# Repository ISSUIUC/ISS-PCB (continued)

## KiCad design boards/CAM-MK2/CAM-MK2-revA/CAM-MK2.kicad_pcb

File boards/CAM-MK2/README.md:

# CAM MK2

The CAM series of custom camera control boards is intended to power and command onboard RunCam FPV cameras for reliable recording of onboard rocket footage.

Bouncing back from the failure of CAM MK1, the team’s onboard video system saw a big leap forward with the success of CAM MK2. In addition to shrinking board size by 33%, MK2 features revamped power circuitry and additional camera control features, making it more flexible as it seeks to ensure proper operation of the vehicle’s cameras for the collection of visual data on in-flight events (and capturing some really cool views). Closely integrated with MIDAS through inter-board CAN and I2C interfaces, CAM is capable of receiving remote commands based on either the MIDAS FSM or telemetry communications from the ground station. As the first peripheral board designed to talk directly with MIDAS, CAM serves as a pioneer of connectivity in the MIDAS ecosystem and has flown successfully several times.

Read more about CAM, MIDAS and the surrounding avionics systems in the [MIDAS MK2 Report](https://uofi.box.com/s/k0ad6ryhxbzwpdwt33lxyxuxpivv3qhj).

# Schematics

Printable PDF schematics, diagrams, and layouts for CAM MK2.1 revA can be found in the PDFs and images folders.

# Graphics

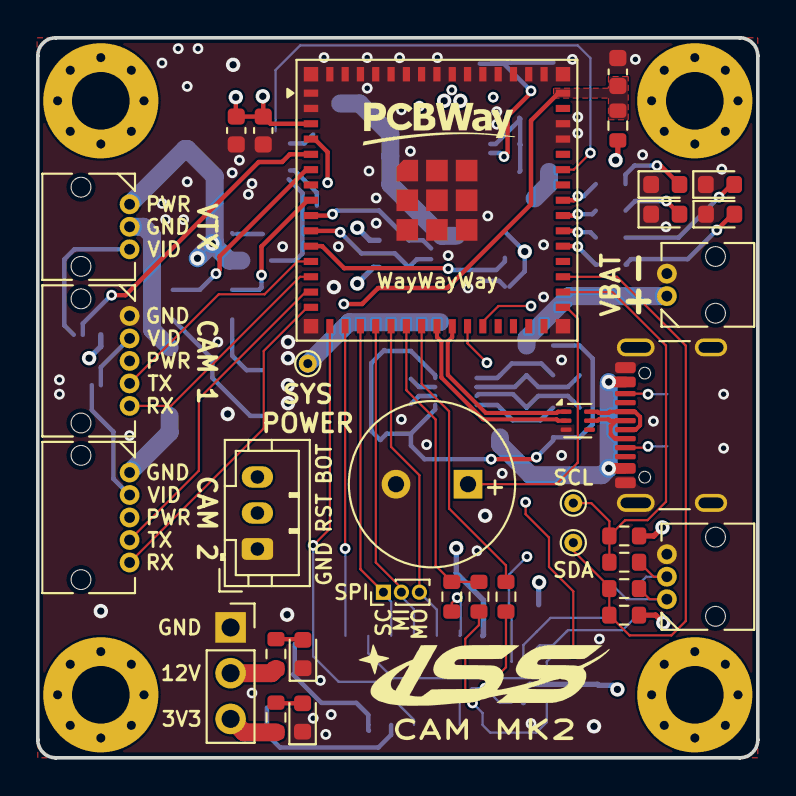
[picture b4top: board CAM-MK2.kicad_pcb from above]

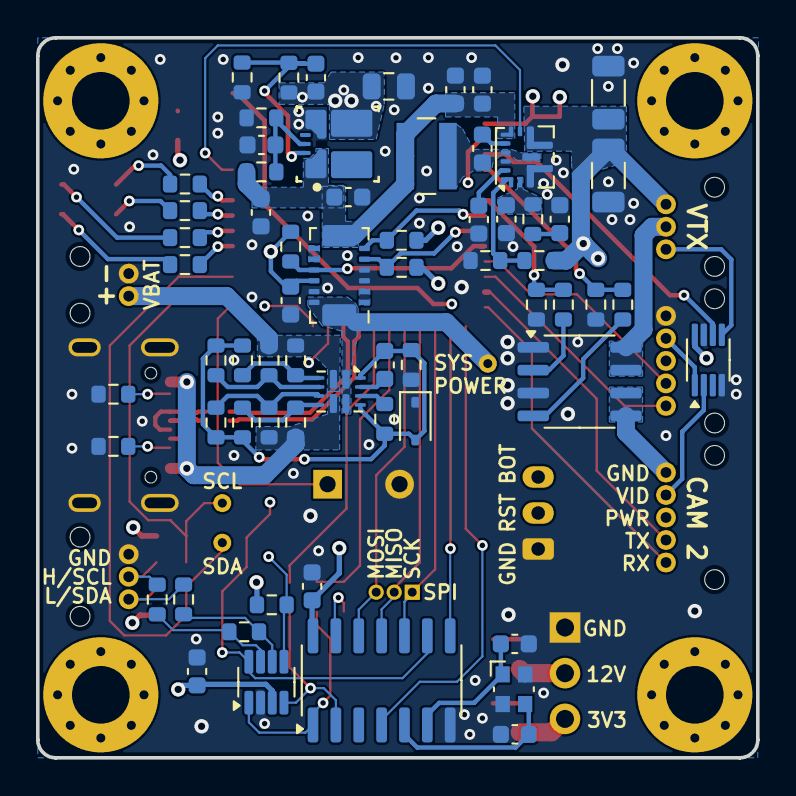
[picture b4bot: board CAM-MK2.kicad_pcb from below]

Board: 4 copper layers, 40.0 x 40.0 mm, 102 parts (64 on the bottom side), 81 nets.

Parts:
BZ101: Buzzer; MagneticBuzzer_PUI_AT-0927-TT-6-R
C101, C102, C111: 22pF; C_0603_1608Metric
C103, C104: 10uF; C_0603_1608Metric
C105, C106, C108, C110, C114, C116, C121: 0.1uF; C_0603_1608Metric
C107: 10nF; C_0603_1608Metric
C109: 2.2uF; C_0603_1608Metric
C112: 47nF; C_0603_1608Metric
C113: 27pF; C_0603_1608Metric
C115: 33uF; C_0805_2012Metric
C117, C118: 47uF; C_1206_3216Metric
C119, C120: 1uF; C_0603_1608Metric
C122: 22uF; C_0603_1608Metric
D101, D104: RED LED; LED_0603_1608Metric
D102, D105: ORANGE LED; LED_0603_1608Metric
D103: BAS416; D_SOD-323
D106: GREEN LED; LED_0603_1608Metric
D107: BLUE LED; LED_0603_1608Metric
H101, H102, H103, H104: MountingHole; MountingHole_3.2mm_M3_Pad_Via
J101: USB4105-GF-A; USB_C_Receptacle_GCT_USB4105-xx-A_16P_TopMnt_Horizontal
J102: 2157601002; Molex_Micro-Lock_2200980271_1x02_P1.25mm_Horizontal
J103, J105: Conn_01x03; Molex_Micro-Lock_2200980371_1x03_P1.25mm_Horizontal
J104, J106: Conn_01x05; Molex_Micro-Lock_2200980571_1x05_P1.25mm_Horizontal
J107: Conn_01x03; JST_PH_B3B-PH-K_1x03_P2.00mm_Vertical
J108: Conn_01x03; PinSocket_1x03_P2.54mm_Vertical
J109: Conn_01x03; PinHeader_1x03_P1.00mm_Vertical
L101: 4.7uH; L_Wuerth_MAPI-4030
Q101: DMNH6022SSDQ; SO-8_3.9x4.9mm_P1.27mm
R101: 22.1k; R_0603_1608Metric
R102, R108, R116, R123, R124, R126, R128, R130: 10k; R_0603_1608Metric
R105, R106: 5.1k; R_0603_1608Metric
R107: 14.3k; R_0603_1608Metric
R109: 135k; R_0603_1608Metric
R110: 30k; R_0603_1608Metric
R111: 931k; R_0603_1608Metric
R112: 48.7k; R_0603_1608Metric
R113, R115, R141, R142, R143, R144: 470; R_0603_1608Metric
R114: 120; R_0603_1608Metric
R117, R122: 4.7k; R_0603_1608Metric
R118, R119, R120, R121, R131, R137, R138, R139: 0; R_0603_1608Metric
R125, R136: 36k; R_0603_1608Metric
R127: 12k; R_0603_1608Metric
R129: 75k; R_0603_1608Metric
R132, R134: 1k; R_0603_1608Metric
R133, R135: 3.3k; R_0603_1608Metric
R140: 20k; R_0603_1608Metric
R145, R146: 2.2k; R_0603_1608Metric
TP101, TP102, TP103: TestPoint; TestPoint_THTPad_D1.0mm_Drill0.5mm
U101: ECMF02-2AMX6; ST_UQFN-6L_1.5x1.7mm_P0.5mm
U102: MCP2518FDT-xSL; SOIC-14_3.9x8.7mm_P1.27mm
U103: TPSM863252; QFN-FCMOD-RDX0007A
U104: TPS61288; Texas_VQFN-HR-20_3x2.5mm_P0.5mm_RQQ0011A
U105: TCAN337G; SOT-23-8
U106: INA745x; VQFN-REL0014B
U107: 74LVC2G157; VSSOP-8_2.3x2mm_P0.5mm
U108: TPS2121; Texas_VQFN-HR-12_2x2.5mm_P0.5mm
U109: ESP32-S3-MINI-1U; ESP32-S2-MINI-1U
Y101: 40MHz; Crystal_SMD_Abracon_ABM10-4Pin_2.5x2.0mm

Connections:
+3V3: C110.2, C111.1, C114.1, C115.1, C116.2, C121.1, C122.1, J108.3, R108.1, R109.1, R113.1, R116.1, R117.1, R122.1, R140.2, R145.2, R146.1, U102.14 (VDD), U103.3 (VOUT), U105.3 (VCC), U106.11 (VS), U107.8 (VCC), U109.3 (3V3)
+12V: C117.1, C118.1, J104.3, J105.1, J106.3, J108.2, R111.1, R115.1, U104.5 (VOUT)
/12V_EN: U104.6 (EN), U109.40 (RXD0)
/BOOT_SW: J107.3, U109.4 (IO0)
/BUZZER: BZ101.1 (-), U109.31 (IO35)
/CAM_2_POW: J106.1, Q101.5 (D2), Q101.6 (D2)
/CANH: R114.2, R120.1, U105.7 (CANH)
/CANL: R114.1, R118.1, U105.6 (CANL)
/CAN_1: R137.1, R138.1, U109.21 (IO17)
/CAN_2: R139.1, U109.22 (IO18)
/CAN_FAULT: R108.2, U105.5 (FAULT), U109.26 (IO26)
/CAN_NCS: R137.2, U102.13 (NCS)
/CAN_NINT: U102.4 (~INT), U109.16 (IO12)
/CAN_NINT1: U102.8 (~INT1/GPIO1), U109.17 (IO13)
/CAN_RXD: R139.2, U102.2 (RXCAN), U105.4 (RXD)
/CAN_SLNT: U102.9 (~INT0/GPIO0/XSTBY), U105.8 (S), U109.25 (IO21)
/CAN_TXD: R138.2, U102.1 (TXCAN), U105.1 (TXD)
/D+: J101.A6 (D+), J101.B6 (D+), U101.6 (D+_out)
/D-: J101.A7 (D-), J101.B7 (D-), U101.5 (D-_out)
/LED_BLUE: R144.1, U109.35 (IO39)
/LED_GREEN: R143.1, U109.36 (IO40)
/LED_ORANGE: R142.1, U109.37 (IO41)
/LED_RED: R141.1, U109.38 (IO42)
/ON_OFF_2: R134.2, R135.1, U109.6 (IO2)
/ON_OFF_VTX: R132.2, R133.1, U109.8 (IO4)
/RESET_SW: C120.1, J107.2, R140.1, U109.45 (EN)
/RX_1: J104.5, U109.13 (IO9)
/RX_2: J106.5, U109.15 (IO11)
/SCL: R121.1, R146.2, TP102.1, U109.32 (IO36)
/SDA: R119.1, R145.1, TP103.1, U109.33 (IO37)
/SENSE_ALERT: R116.2, U106.10 (ALERT), U109.11 (IO7)
/SENSE_SCL: R122.2, U106.6 (SCL), U109.9 (IO5)
/SENSE_SDA: R117.2, U106.5 (SDA), U109.10 (IO6)
/SPI_MISO: J109.2, U102.11 (SDI), U109.19 (IO15)
/SPI_MOSI: J109.3, U102.12 (SDO), U109.20 (IO16)
/SPI_SCK: J109.1, U102.10 (SCK), U109.18 (IO14)
/SYS_POWER: TP101.1, U106.13 (VBUS), U106.14 (IS+), U108.1 (OUT), U108.8 (OUT)
/TX_1: J104.4, U109.12 (IO8)
/TX_2: J106.4, U109.14 (IO10)
/USB_D+: U101.1 (D+_in), U109.24 (IO20)
/USB_D-: U101.2 (D-_in), U109.23 (IO19)
/USB_POWER: J101.A4 (VBUS), J101.A9 (VBUS), J101.B4 (VBUS), J101.B9 (VBUS), R123.1, R125.1, U108.7 (IN1)
/VBAT: J102.1, R127.1, R129.1, U108.2 (IN2)
/VIDEO_1: J104.2, U107.1 (A)
/VIDEO_2: J106.2, U107.2 (B)
/VIDEO_OUT: J105.3, U107.5 (Y)
/VIDEO_SELECT: U107.6 (~A/B), U109.5 (IO1)
/VREG_IN: C103.1, C104.1, C105.1, C106.1, L101.1, R101.1, U103.1 (VIN), U104.7 (VIN), U106.7 (IS-)
/VTX_POW: J105.2, Q101.7 (D1), Q101.8 (D1)
GND: BZ101.2 (+), C101.1, C102.2, C103.2, C104.2, C105.2, C106.2, C107.2, C109.2, C110.1, C112.2, C113.2, C114.2, C115.2, C116.1, C117.2, C118.2, C120.2, C121.2, C122.2, D101.1 (K), D102.1 (K), D103.1 (K), D104.1 (K), D105.1 (K), D106.1 (K), D107.1 (K), J101.A1 (GND), J101.A12 (GND), J101.B1 (GND), J101.B12 (GND), J101.S1 (SHIELD), J102.2, J103.3, J104.1, J107.1, J108.1, Q101.1 (S1), Q101.3 (S2), R102.2, R105.1, R106.1, R110.2, R112.2, R131.2, R133.2, R135.2, U101.3 (GND), U102.7 (VSS), U103.4 (PGND), U104.3 (PGND), U104.10 (AGND), U105.2 (GND), U106.3 (A1), U106.4 (A0), U106.12 (GND), U107.4 (GND), U107.7 (~G), U109.1 (GND), U109.2 (GND), U109.42 (GND), U109.43 (GND), U109.46 (GND), U109.47 (GND), U109.48 (GND), U109.49 (GND), U109.50 (GND), U109.51 (GND), U109.52 (GND), U109.53 (GND), U109.54 (GND), U109.55 (GND), U109.56 (GND), U109.57 (GND), U109.58 (GND), U109.59 (GND), U109.60 (GND), U109.61 (GND), U109.62 (GND), U109.63 (GND), U109.64 (GND), U109.65 (GND), Y101.2, Y101.4
unnamed: C108.1, L101.2, U104.4 (SW), U104.9 (SW)
unnamed: C112.1, R107.2
unnamed: D101.2 (A), R113.2
unnamed: D102.2 (A), R115.2
unnamed: C119.1, D103.2 (A), R124.2, R126.2, R128.2, R130.2, R131.1, R136.1, U108.9 (ST), U108.12 (GND)
unnamed: D104.2 (A), R141.2
unnamed: D105.2 (A), R142.2
unnamed: D106.2 (A), R143.2
unnamed: D107.2 (A), R144.2
unnamed: J101.A5 (CC1), R105.2
unnamed: J101.B5 (CC2), R106.2
unnamed: J103.1, R118.2, R119.2
unnamed: J103.2, R120.2, R121.2
unnamed: Q101.2 (G1), R132.1
unnamed: Q101.4 (G2), R134.1
unnamed: C102.1, U102.6 (OSC1), Y101.1
unnamed: C101.2, U102.5 (OSC2), Y101.3
unnamed: C107.1, R101.2, R102.1, U103.6 (EN)
unnamed: C111.2, R109.2, R110.1, U103.7 (FB)
unnamed: C108.2, U104.8 (BST)
unnamed: C113.1, R107.1, U104.2 (COMP)
unnamed: R111.2, R112.1, U104.1 (FB)
unnamed: C109.1, U104.11 (VCC)
unnamed: U106.1 (SH+), U106.2 (IN+)
unnamed: U106.8 (SH-), U106.9 (IN-)
unnamed: R127.2, R128.1, U108.3 (CP2)
unnamed: R136.2, U108.10 (ILM)
unnamed: R125.2, R126.1, U108.5 (OV1)
unnamed: R129.2, R130.1, U108.4 (OV2)
unnamed: R123.2, R124.1, U108.6 (PR1)
unnamed: C119.2, U108.11 (SS)

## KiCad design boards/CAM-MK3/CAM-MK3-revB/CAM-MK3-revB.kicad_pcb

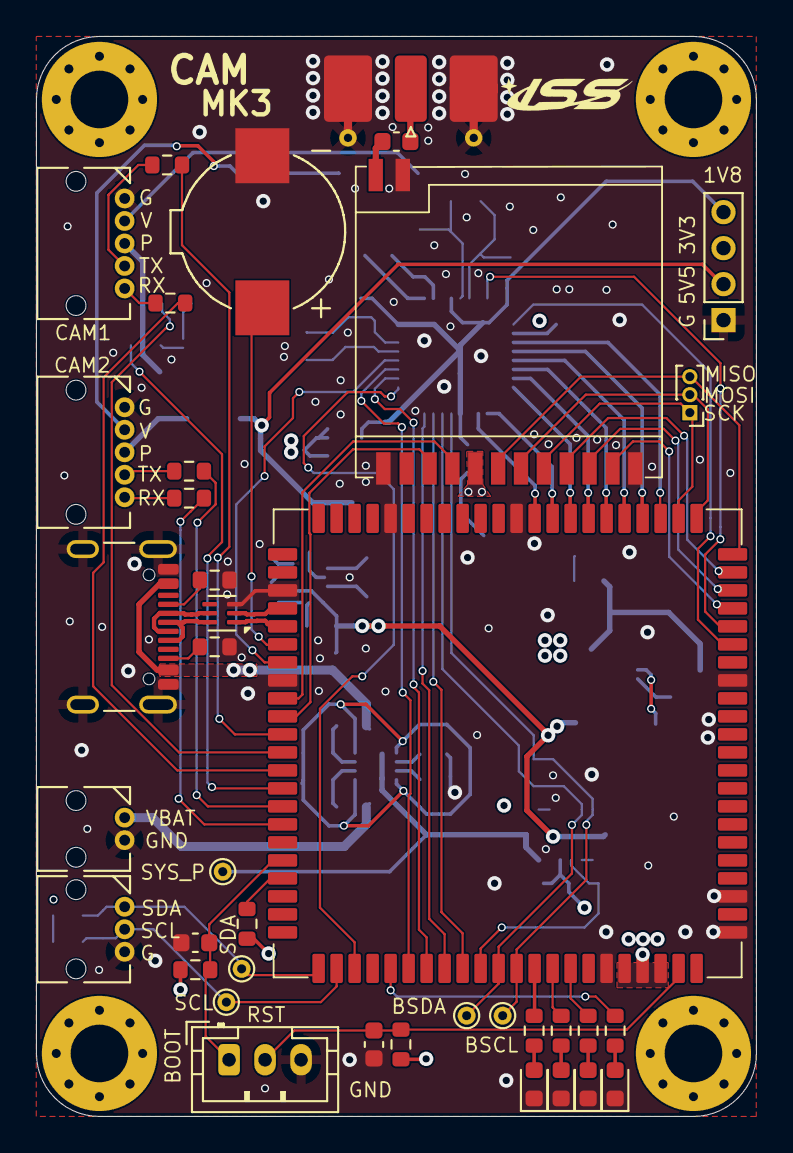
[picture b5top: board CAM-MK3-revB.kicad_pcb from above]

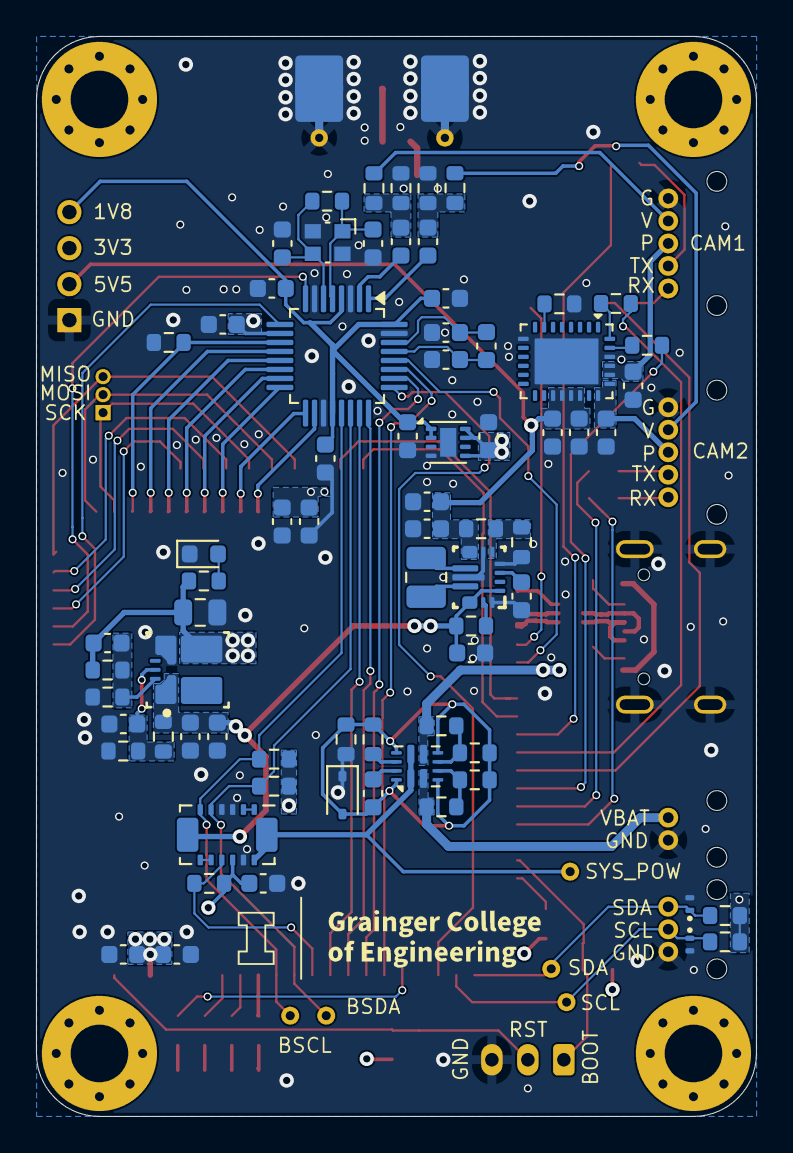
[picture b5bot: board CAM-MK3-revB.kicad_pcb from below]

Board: 4 copper layers, 40.0 x 60.0 mm, 115 parts (73 on the bottom side), 97 nets.

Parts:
BZ101: Buzzer; Buzzer_SMTB-0927-TW-R
C101, C106, C108, C109, C110, C111, C112, C114, C116, C117, C118, C121, C203, C204: 100nF; C_0603_1608Metric
C102, C103: 19pF; C_0603_1608Metric
C104, C105, C107, C115, C123, C210, C211, C212: 1uF; C_0603_1608Metric
C113: 22uF; C_0603_1608Metric
C119, C120: 22nF; C_0603_1608Metric
C122: 100pF; C_0603_1608Metric
C201, C202, C208: 10uF; C_0603_1608Metric
C205: 10nF; C_0603_1608Metric
C206: 22pF; C_0603_1608Metric
C207: 47uF; C_0603_1608Metric
C209: 33uF; C_0805_2012Metric
D101, D106: ESD321; Texas_DPY0002A_0.6x1mm_P0.65mm
D102, D202: RED LED; LED_0603_1608Metric
D103: ORANGE LED; LED_0603_1608Metric
D104: GREEN LED; LED_0603_1608Metric
D105: BLUE LED; LED_0603_1608Metric
D201: BAS416; D_SOD-323
H101, H102, H103, H104: MountingHole; MountingHole_3.2mm_M3_Pad_Via
J101: USB4105-GF-A; USB_C_Receptacle_GCT_USB4105-xx-A_16P_TopMnt_Horizontal
J102: 2200980271; Molex_Micro-Lock_2200980271_1x02_P1.25mm_Horizontal
J103: Conn_01x03; PinHeader_1x03_P1.00mm_Vertical
J104, J107: Conn_01x05; Molex_Micro-Lock_2200980571_1x05_P1.25mm_Horizontal
J105: Conn_01x03; Molex_Micro-Lock_2200980371_1x03_P1.25mm_Horizontal
J106: SMA; SMA_Molex_73251-2120_EdgeMount_Horizontal
J108: Conn_01x03; JST_PH_B3B-PH-K_1x03_P2.00mm_Vertical
J111: Conn_01x04; PinSocket_1x04_P2.00mm_Vertical
L201: 1.5uH; L_1008_2520Metric
R101, R102, R103, R104: 37.4; R_0603_1608Metric
R105, R210: 100k; R_0603_1608Metric
R106, R107: 10K; R_0603_1608Metric
R108, R109, R110, R120, R201, R203: 10k; R_0603_1608Metric
R111: 680; R_0603_1608Metric
R112, R113, R205, R207: 5.1k; R_0603_1608Metric
R114, R115: 4.7k; R_0603_1608Metric
R116, R117, R118, R119: 220; R_0603_1608Metric
R121, R122, R123, R124, R214: 470; R_0603_1608Metric
R125, R127: 2.2k; R_0603_1608Metric
R126: 20k; R_0603_1608Metric
R202: 22.1k; R_0603_1608Metric
R204: 19.6k; R_0603_1608Metric
R206: 39k; R_0603_1608Metric
R208: 0; R_0603_1608Metric
R209: 590k; R_0603_1608Metric
R211: 135k; R_0603_1608Metric
R212: 30k; R_0603_1608Metric
R213: 21.5k; R_0603_1608Metric
TP101, TP102, TP103, TP104, TP201: TestPoint; TestPoint_THTPad_D1.0mm_Drill0.5mm
U101: ESP32-P4-Module
U102: TVP5151; LQFP-32_5x5mm_P0.5mm
U103: RF4463PRO
U104: ECMF02-2AMX6; ST_UQFN-6L_1.5x1.7mm_P0.5mm
U105: TPS274160B; WQFN-RLH0028A
U106: INA745x; VQFN-REL0014B
U201: TPS63070; VQFN-RNM0015A
U202: TPSM863252; QFN-FCMOD-RDX0007A
U203: TPS2121; Texas_VQFN-HR-12_2x2.5mm_P0.5mm
U204: TPS7A21-Q1; Texas_DSG0008A_WSON-8-1EP_2x2mm_P0.5mm_EP0.9x1.6mm
Y101: ABM10; Crystal_SMD_Abracon_ABM10-4Pin_2.5x2.0mm

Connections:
+1V8: C109.2, C112.2, C114.2, C212.1, J111.4, U102.4 (PLL_AVDD), U102.20 (DVDD), U102.32 (CH_AVDD), U204.1 (OUT), U204.2 (OUT)
+3V3: C108.1, C110.1, C113.1, C115.1, C116.1, C121.1, C206.1, C209.1, C211.1, J111.3, R106.2, R107.2, R114.1, R115.1, R120.1, R125.2, R126.2, R127.1, R211.1, R214.1, U101.84 (ESP_VBAT), U101.85 (ESP_3V3), U101.86 (ESP_3V3), U102.10 (IO_DVDD), U103.5 (VCC), U106.11 (VS), U202.3 (VOUT), U204.5 (EN), U204.7 (IN), U204.8 (IN)
+5V5: C117.1, C118.1, C207.1, C208.1, J111.2, R209.1, U105.17 (VS), U105.18 (VS), U105.19 (VS), U105.20 (VS), U201.7 (VOUT), U201.8 (VOUT)
/AVID: U101.73 (GPIO45), U102.26 (AVID/CLK_IN)
/BOARD_SCL: R115.2, TP103.1, U101.78 (GPIO50), U102.21 (SCL), U106.6 (SCL)
/BOARD_SDA: R114.2, TP104.1, U101.77 (GPIO49), U102.22 (SDA), U106.5 (SDA)
/BOOT_SW: C111.1, J108.1, R107.1, U101.62 (GPIO35)
/BUZZER: BZ101.1 (-), U101.50 (GPIO24)
/CAM_1_POW: C120.1, J104.3, U105.24 (OUT1), U105.25 (OUT1)
/CAM_2_POW: C119.1, J107.3, U105.22 (OUT2), U105.23 (OUT2)
/D+: J101.A6 (D+), J101.B6 (D+), U104.6 (D+_out)
/D-: J101.A7 (D-), J101.B7 (D-), U104.5 (D-_out)
/FID/GLCO: U101.75 (GPIO47), U102.23 (FID/GLCO)
/GPCL/VBLK: U101.72 (GPIO44), U102.27 (INTREQ/GPCL/VBLK)
/HSYNC: U101.69 (GPIO41), U102.25 (HSYNC)
/LED_BLUE: R124.1, U101.71 (GPIO43)
/LED_GREEN: R123.1, U101.81 (GPIO53)
/LED_ORANGE: R122.1, U101.80 (GPIO52)
/LED_RED: R121.1, U101.79 (GPIO51)
/ON_OFF_1: R109.1, U101.58 (GPIO31)
/ON_OFF_2: R110.1, U101.56 (GPIO29)
/PDN: U101.51 (GPIO25), U102.28 (PDN)
/Power/PMUX_GND: C210.1, D201.2 (A), R205.2, R207.2, R208.1, R213.1, U203.3 (CP2), U203.6 (PR1), U203.9 (ST), U203.12 (GND)
/RESET_SW: C123.1, J108.2, R126.1, U101.87 (CHIP_PU)
/RESET_VD: U101.18 (GPIO3), U102.8 (RESETB)
/RX_1: R116.2, U101.57 (GPIO30)
/RX_2: R118.2, U101.60 (GPIO33)
/SCL: D106.1 (K), J105.2, R127.2, TP101.1, U101.68 (GPIO40)
/SCLK: U101.17 (GPIO2), U102.9 (SCLK)
/SDA: D101.1 (K), J105.1, R125.1, TP102.1, U101.67 (GPIO39)
/SENSE_ALERT: R120.2, U101.76 (GPIO48), U106.10 (ALERT)
/SPI_MISO: J103.3, U101.22 (GPIO7), U103.6 (SD0)
/SPI_MOSI: J103.2, U101.23 (GPIO8), U103.7 (SDI)
/SPI_SCK: J103.1, U101.24 (GPIO9), U103.8 (SCLK)
/SYS_POWER: TP201.1, U106.13 (VBUS), U106.14 (IS+), U203.1 (OUT), U203.8 (OUT)
/Si4463_ANT: C122.2, U103.14 (ANT)
/Si4463_CS: U101.21 (GPIO6), U103.9 (nSEL)
/Si4463_EN: U101.19 (GPIO4), U103.11 (SDN)
/Si4463_GPIO0: U101.54 (GPIO27), U103.3 (GPIO0)
/Si4463_GPIO1: U101.53 (GPIO26), U103.4 (GPIO1)
/Si4463_nIRQ: U101.20 (GPIO5), U103.10 (nIRQ)
/TX_1: R117.2, U101.55 (GPIO28)
/TX_2: R119.2, U101.59 (GPIO32)
/USB_D+: U101.49 (DP), U104.1 (D+_in)
/USB_D-: U101.48 (DM), U104.2 (D-_in)
/USB_POWER: J101.A4 (VBUS), J101.A9 (VBUS), J101.B4 (VBUS), J101.B9 (VBUS), R204.1, U203.7 (IN1)
/VBAT: J102.1, R206.1, U203.2 (IN2)
/VIDEO_1: J104.2, R102.1
/VIDEO_2: J107.2, R104.1
/VREG_IN: C201.1, C202.1, C203.1, R201.1, R202.1, U106.7 (IS-), U201.1 (PS_SYNC), U201.12 (VIN), U201.13 (VIN), U202.1 (VIN)
/VSYNC: U101.74 (GPIO46), U102.24 (VSYNC/PALI)
/YOUT0: U101.32 (GPIO23), U102.18 (YOUT0)
/YOUT1: U101.31 (GPIO22), U102.17 (YOUT1)
/YOUT2: U101.30 (GPIO21), U102.16 (YOUT2)
/YOUT3: U101.29 (GPIO20), U102.15 (YOUT3)
/YOUT4: U101.28 (GPIO13), U102.14 (YOUT4)
/YOUT5: U101.27 (GPIO12), U102.13 (YOUT5)
/YOUT6: U101.26 (GPIO11), U102.12 (YOUT6)
/YOUT7: R108.2, U101.25 (GPIO10), U102.11 (YOUT7/I2CSEL)
GND: BZ101.2 (+), C102.1, C103.1, C104.1, C105.1, C108.2, C109.1, C110.2, C111.2, C112.1, C113.2, C114.1, C115.2, C116.2, C117.2, C118.2, C119.2, C120.2, C121.2, C123.2, C201.2, C202.2, C203.2, C204.2, C205.2, C207.2, C208.2, C209.2, C211.2, C212.2, D101.2 (A), D102.1 (K), D103.1 (K), D104.1 (K), D105.1 (K), D106.2 (A), D201.1 (K), D202.1 (K), J101.A1 (GND), J101.A12 (GND), J101.B1 (GND), J101.B12 (GND), J101.S1 (SHIELD), J102.2, J104.1, J105.3, J106.2 (Ext), J107.1, J108.3, J111.1, R101.1, R103.1, R108.1, R111.2, R112.1, R113.1, R203.2, R208.2, R210.2, R212.2, U101.1 (GND), U101.3 (GND), U101.15 (GND), U101.33 (GND), U101.40 (GND), U101.47 (GND), U101.52 (GND), U101.83 (GND), U102.3 (PLL_AGND), U102.7 (AGND), U102.19 (DGND), U102.31 (CH_AGND), U103.1 (GND), U103.12 (GND), U103.13 (GND), U104.3 (GND), U105.9 (GND), U105.26 (GND), U105.29 (PowerPAD), U106.3 (A1), U106.4 (A0), U106.12 (GND), U201.4 (GND), U201.6 (FB2), U201.10 (PGND), U201.15 (VSEL), U202.4 (PGND), U204.4 (GND), U204.9 (EPAD), Y101.2, Y101.4
unnamed: C101.1, R101.2, R102.2
unnamed: C106.1, R103.2, R104.2
unnamed: D102.2 (A), R121.2
unnamed: D103.2 (A), R122.2
unnamed: D104.2 (A), R123.2
unnamed: D105.2 (A), R124.2
unnamed: D202.2 (A), R214.2
unnamed: J101.A5 (CC1), R112.2
unnamed: J101.B5 (CC2), R113.2
unnamed: J104.4, R117.1
unnamed: J104.5, R116.1
unnamed: C122.1, J106.1 (In)
unnamed: J107.4, R119.1
unnamed: J107.5, R118.1
unnamed: R106.1, U101.63 (GPIO36)
unnamed: C106.2, U102.1 (AIP1A)
unnamed: C101.2, U102.2 (AIP1B)
unnamed: C105.2, C107.2, U102.30 (REFM)
unnamed: C104.2, C107.1, U102.29 (REFP)
unnamed: C103.2, R105.1, U102.5 (XTAL1/OSC), Y101.1
unnamed: C102.2, R105.2, U102.6 (XTAL2), Y101.3
unnamed: R111.1, U105.7 (CL)
unnamed: R109.2, U105.27 (EN1)
unnamed: R110.2, U105.28 (EN2)
unnamed: U106.1 (SH+), U106.2 (IN+)
unnamed: U106.8 (SH-), U106.9 (IN-)
unnamed: R201.2, U201.14 (EN)
unnamed: R209.2, R210.1, U201.5 (FB)
unnamed: L201.1, U201.11 (L1)
unnamed: L201.2, U201.9 (L2)
unnamed: C204.1, U201.3 (VAUX)
unnamed: C205.1, R202.2, R203.1, U202.6 (EN)
unnamed: C206.2, R211.2, R212.1, U202.7 (FB)
unnamed: R213.2, U203.10 (ILM)
unnamed: R204.2, R205.1, U203.5 (OV1)
unnamed: R206.2, R207.1, U203.4 (OV2)
unnamed: C210.2, U203.11 (SS)
